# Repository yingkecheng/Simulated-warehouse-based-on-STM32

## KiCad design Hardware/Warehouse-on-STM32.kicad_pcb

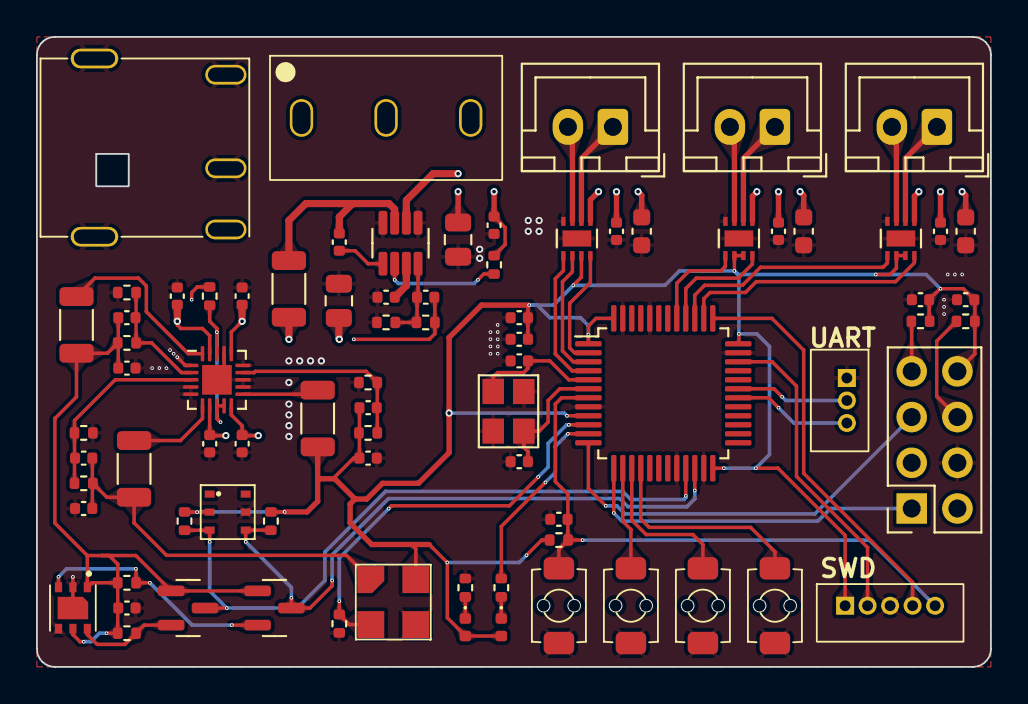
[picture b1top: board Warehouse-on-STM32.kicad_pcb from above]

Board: 2 copper layers, 53.0 x 35.0 mm, 80 parts (0 on the bottom side), 54 nets.

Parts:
C1, C4, C8, C9, C10, C14, C16, C18: 10uF; C_0402_1005Metric
C2, C3, C6, C19, C20, C21, C27, C28, C29, C30: 104; C_0402_1005Metric
C5, C7, C22: 33pF; C_0402_1005Metric
C11, C12, C13: 220pF; C_0402_1005Metric
C15: 1uF; C_0402_1005Metric
C17, C23: 22uF; C_0805_2012Metric
C24, C25, C26: 10uF; C_0603_1608Metric
D1: RED; LED_0402_1005Metric
D2: BLUE; LED_0402_1005Metric
J1: ESP8266; PinSocket_2x04_P2.54mm_Vertical
J2: SWD; 1.25-5A
J3: UART; 1.25-3A
J4: Barrel_Jack_Switch_MountingPin; BarrelJack_XKB_DC-044A-2.5A-2.5
J5, J6, J7: Conn_01x02; JST_XH_B2B-XH-A_1x02_P2.50mm_Vertical
L1, L2, L3: 1.5uH; L_1206_3216Metric
L4: 4.7uH; L_1206_3216Metric
Q1, Q2: AO3400A; SOT-23
R1, R2, R3, R4, R5: 10K; R_0402_1005Metric
R6: 510K; R_0402_1005Metric
R7: 110K; R_0402_1005Metric
R8: 470K; R_0402_1005Metric
R9: 150K; R_0402_1005Metric
R10: 200K; R_0402_1005Metric
R11, R12, R13: 100K; R_0402_1005Metric
R14: 40.2K; R_0402_1005Metric
R15: 5.49K; R_0402_1005Metric
R16, R17, R18, R20: 4.7K; R_0402_1005Metric
R19: 1M; R_0402_1005Metric
SW1, SW2, SW3, SW4: SW_Push; SW_XKB_TS-1185-B-A-B-A
SW5: SW_XKB_SS-12D10L5
U1: STM32F103C8Tx; LQFP-48_7x7mm_P0.5mm
U2: EA3036C; QFN-20-1EP_3x3mm_P0.4mm_EP1.65x1.65mm
U3: MP2225GJ; TSOT-23-8
U4, U5, U6: DRV8820DSG; WSON-8-1EP_2x2mm_P0.5mm_EP0.9x1.6mm
U7: AHT20
U8: SGP30
U9: Sensor; MEMS气体传感器
Y1: 8MHz; Crystal_SMD_3225-4Pin_3.2x2.5mm

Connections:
+1V8: C10.1, C13.1, C30.1, L3.1, Q1.1 (G), Q2.1 (G), R10.1, R18.1, R20.1, U8.1 (VDD), U8.5 (VDDH)
+2V5: C9.1, C12.1, L2.1, R8.1, U9.1 (VH)
+3V3: C1.1, C2.1, C4.1, C6.1, C8.1, C11.1, D1.2 (A), D2.2 (A), J1.8, J2.1, L1.1, R1.1, R2.1, R5.1, R6.1, R16.1, R17.1, U1.1 (VBAT), U1.9 (VDDA), U1.24 (VDD), U1.36 (VDD), U1.48 (VDD), U4.7 (MODE), U5.6 (IN1/PH), U5.7 (MODE), U6.6 (IN1/PH), U6.7 (MODE), U7.2 (VDD), U9.4 (VCC)
+5V: C14.1, C15.1, C16.1, C18.1, C22.1, C23.1, L4.2, R12.1, R14.1, U2.7 (VIN2), U2.10 (VIN1), U2.16 (VCC), U2.19 (VIN3)
+12V: C17.1, C19.1, C24.1, C25.1, C26.1, C27.1, C28.1, C29.1, R13.1, SW5.3, U3.2 (IN), U4.1 (VM), U5.1 (VM), U6.1 (VM)
/ADC: R19.1, U1.10 (PA0), U9.2 (OUT)
/AEN: U1.4 (PC15), U4.5 (IN2/EN)
/APH: U1.3 (PC14), U4.6 (IN1/PH)
/ASLEEP: U1.2 (PC13), U4.8 (~SLEEP)
/BEN: U1.41 (PB5), U5.5 (IN2/EN)
/BSLEEP: U1.40 (PB4), U5.8 (~SLEEP)
/CEN: U1.39 (PB3), U6.5 (IN2/EN)
/CSLEEP: U1.38 (PA15), U6.8 (~SLEEP)
/ESP_RX: J1.1, U1.13 (PA3)
/ESP_TX: J1.5, U1.12 (PA2)
/KEY0: SW1.2, U1.16 (PA6)
/KEY1: SW2.2, U1.15 (PA5)
/KEY2: SW3.2, U1.14 (PA4)
/LED0: R4.2, U1.11 (PA1)
/NRST: C3.1, J2.5, R5.2, SW4.2, U1.7 (NRST)
/SCL: Q1.3 (D), R16.2, U1.21 (PB10), U7.3 (SCL)
/SDA: Q2.3 (D), R17.2, U1.22 (PB11), U7.4 (SDA)
/SWCLK: J2.4, U1.37 (PA14)
/SWDIO: J2.2, U1.34 (PA13)
/USART1_RX: J3.2, U1.31 (PA10)
/USART1_TX: J3.3, U1.30 (PA9)
/传感器模块/SCL1V8: Q1.2 (S), R20.2, U8.6 (SCL)
/传感器模块/SDA1V8: Q2.2 (S), R18.2, U8.3 (SDA)
GND: C1.2, C2.2, C3.2, C4.2, C5.2, C6.2, C7.2, C8.2, C9.2, C10.2, C14.2, C15.2, C16.2, C17.2, C18.2, C19.2, C20.1, C23.2, C24.2, C25.2, C26.2, C27.2, C28.2, C29.2, C30.2, J1.4, J2.3, J3.1, J4.2, J4.3, J4.MP (MountPin), R3.2, R7.1, R9.1, R11.1, R15.2, R19.2, SW1.1, SW2.1, SW3.1, SW4.1, U1.8 (VSSA), U1.20 (PB2), U1.23 (VSS), U1.35 (VSS), U1.44 (BOOT0), U1.47 (VSS), U2.1 (GND3), U2.4 (GND2), U2.5 (GND2), U2.12 (GND1), U2.13 (GND1), U2.15 (AGND), U2.17 (AGND), U2.21 (EP), U3.1 (AGND), U3.4 (GND), U4.4 (GND), U4.9 (GND), U5.4 (GND), U5.9 (GND), U6.4 (GND), U6.9 (GND), U7.5 (GND), U8.2 (VSS), U8.4 (R), U8.7, U9.3 (GND), Y1.2, Y1.4
unnamed: D1.1 (K), R3.1
unnamed: D2.1 (K), R4.1
unnamed: J1.6, R2.2
unnamed: J1.7, R1.2
unnamed: J4.1, SW5.2
unnamed: J5.1, U4.2 (OUT1)
unnamed: J5.2, U4.3 (OUT2)
unnamed: J6.1, U5.2 (OUT1)
unnamed: J6.2, U5.3 (OUT2)
unnamed: J7.1, U6.2 (OUT1)
unnamed: J7.2, U6.3 (OUT2)
unnamed: C5.1, U1.5 (PD0), Y1.1
unnamed: C7.1, U1.6 (PD1), Y1.3
unnamed: R12.2, U2.8 (EN2), U2.9 (EN1), U2.18 (EN3)
unnamed: C11.2, R6.2, R7.2, U2.14 (FB1)
unnamed: C12.2, R8.2, R9.2, U2.3 (FB2)
unnamed: C13.2, R10.2, R11.2, U2.2 (FB3)
unnamed: L1.2, U2.11 (LX1)
unnamed: L2.2, U2.6 (LX2)
unnamed: L3.2, U2.20 (LX3)
unnamed: C21.1, U3.5 (BST)
unnamed: R13.2, U3.6 (EN/SYNC)
unnamed: C22.2, R14.2, R15.1, U3.8 (FB)
unnamed: C21.2, L4.1, U3.3 (SW)
unnamed: C20.2, U3.7 (VCC)

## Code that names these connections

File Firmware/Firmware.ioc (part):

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Mcu.Name=STM32F103C(8-B)Tx
Mcu.Package=LQFP48
Mcu.UserName=STM32F103C8Tx
PA1.GPIOParameters=GPIO_Label
PA1.GPIO_Label=LED
PA1.Signal=GPIO_Output
PA10.Mode=Asynchronous
PA10.Signal=USART1_RX
PA13.Mode=Serial_Wire
PA13.Signal=SYS_JTMS-SWDIO
PA14.Mode=Serial_Wire
PA14.Signal=SYS_JTCK-SWCLK
PA15.GPIOParameters=GPIO_Label
PA15.GPIO_Label=C_SLP
PA15.Signal=GPIO_Output
PA2.Mode=Asynchronous
PA2.Signal=USART2_TX
PA3.Mode=Asynchronous
PA3.Signal=USART2_RX
PA4.GPIOParameters=GPIO_PuPd,GPIO_Label
PA4.GPIO_Label=KEY2
PA4.GPIO_PuPd=GPIO_PULLUP
PA4.Signal=GPIO_Input
PA5.GPIOParameters=GPIO_PuPd,GPIO_Label
PA5.GPIO_Label=KEY1
PA5.GPIO_PuPd=GPIO_PULLUP
PA5.Signal=GPIO_Input
PA6.GPIOParameters=GPIO_PuPd,GPIO_Label
PA6.GPIO_Label=KEY0
PA6.GPIO_PuPd=GPIO_PULLUP
PA6.Signal=GPIO_Input
PA9.Mode=Asynchronous
PA9.Signal=USART1_TX
PB10.Mode=I2C
PB10.Signal=I2C2_SCL
PB11.Mode=I2C
PB11.Signal=I2C2_SDA
PB3.GPIOParameters=GPIO_Label
PB3.GPIO_Label=C_EN
PB3.Signal=GPIO_Output
PB4.GPIOParameters=GPIO_Label
PB4.GPIO_Label=B_SLP
PB4.Signal=GPIO_Output
PB5.GPIOParameters=GPIO_Label
PB5.GPIO_Label=B_EN
PB5.Signal=GPIO_Output
PC13-TAMPER-RTC.GPIOParameters=GPIO_Label
PC13-TAMPER-RTC.GPIO_Label=A_SLP
PC13-TAMPER-RTC.Signal=GPIO_Output
PC14-OSC32_IN.GPIOParameters=GPIO_Label
PC14-OSC32_IN.GPIO_Label=A_PH
PC14-OSC32_IN.Signal=GPIO_Output
PC15-OSC32_OUT.GPIOParameters=GPIO_Label
PC15-OSC32_OUT.GPIO_Label=A_EN
PC15-OSC32_OUT.Signal=GPIO_Output
PD0-OSC_IN.Mode=HSE-External-Oscillator
PD0-OSC_IN.Signal=RCC_OSC_IN
PD1-OSC_OUT.Mode=HSE-External-Oscillator
PD1-OSC_OUT.Signal=RCC_OSC_OUT
RCC.SYSCLKFreq_VALUE=72000000
RCC.SYSCLKSource=RCC_SYSCLKSOURCE_PLLCLK
board=custom

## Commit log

2023-03-09 添加应硬件设计
2023-03-09 fisrt commit
2023-03-16 下班前提交初版
2023-03-27 完成最小系统的电路原理图设计
2023-03-28 完成传感器模块原理图
2023-03-28 完成电源模块电路原理图
2023-03-28 运行DRC前
2023-03-29 2023/3/29
2023-04-05 完成布局
2023-04-06 完成部分布线
2023-04-06 绘制第一版
2023-04-18 version 1.0
2023-04-19 修改了电机驱动芯片旁的电容封装为0603
2023-05-10 coding
2023-05-12 Add state diagram.
2023-05-13 PCB V2
